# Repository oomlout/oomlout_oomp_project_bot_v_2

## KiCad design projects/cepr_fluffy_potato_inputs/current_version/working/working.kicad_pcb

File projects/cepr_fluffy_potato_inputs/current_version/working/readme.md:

# fluffy_potato
 
## summary 
* id: cepr_fluffy_potato_inputs
* user: cepr
* name: fluffy_potato
* board: inputs
* repo: https://github.com/cepr/fluffy-potato
* src_file_repo_kicad_pcb: inputs/kicad/inputs.kicad_pcb
* src_file_repo_kicad_pcb_link: https://github.com/cepr/fluffy-potato/tree/master/inputs/kicad/inputs.kicad_pcb

* src_file_repo_sch: board_generator/modules/switch-lowside-6a/switch-lowside-6a.sch
* src_file_repo_sch_link: https://github.com/cepr/fluffy-potato/tree/master/board_generator/modules/switch-lowside-6a/switch-lowside-6a.sch
* full details link: https://github.com/oomlout/oomlout_oomp_project_bot_v_2/tree/main/projects/cepr_fluffy_potato_inputs/current_version/working

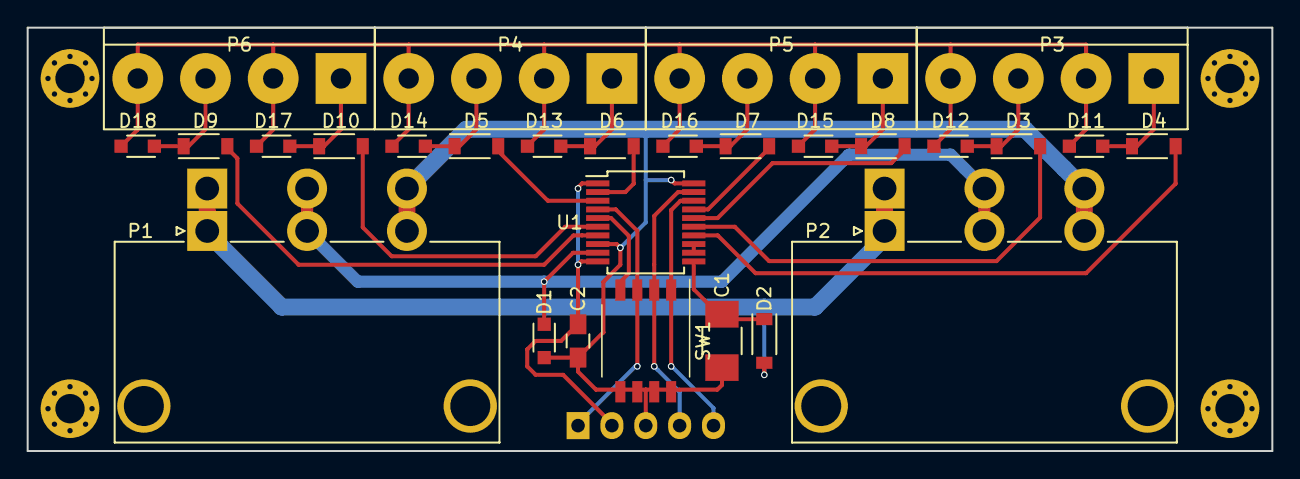
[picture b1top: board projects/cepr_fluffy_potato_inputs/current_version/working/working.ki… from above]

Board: 2 copper layers, 93.3 x 31.7 mm, 29 parts (1 on the bottom side), 26 nets.

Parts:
C1: 10uF; C_1210_HandSoldering
C2: 1uF; C_0805_HandSoldering
D1, D11, D12, D13, D14, D15, D16, D17, D18: RSB36V; SOD-323_HandSoldering
D2, D3, D4, D5, D6, D7, D8, D9, D10: 1N4148W-7-F; SOD-123
P1, P2: MOLEX-0431603103; Molex_Sabre_43160-XX03_03x7.49mm_Angled_BoardLock
P3, P4, P5, P6: TE-282836-4; bornier4
P7: CONN_01X05; Pin_Header_Angled_1x05
SW1: SW_DIP_x04; SW_DIP_x4_W7.62mm_Slide_Copal_CHS-B
U1: PIC16F1829LIN; SSOP-20_5.3x7.2mm_Pitch0.65mm

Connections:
/IN0: D4.2, U1.14
/IN1: D3.2, U1.15
/IN2: D8.2, U1.16
/IN3: D7.2, U1.17
/IN4: D6.2, U1.2
/IN5: D5.2, U1.3
/IN6: D10.2, U1.6
/IN7: D9.2, U1.7
/Sheet584DA639/+5V: C2.1, P7.2, U1.1, U1.10
/Sheet584DA639/+12V: C1.1, D2.1, U1.11
/Sheet584DA639/LBUS: D1.1, P1.2, P2.2, U1.9
/lin_common/12V_UNPROTECTED: D2.2, P1.1, P2.1
/lin_common/A0: P7.5, SW1.1, U1.18
/lin_common/A1: P7.4, SW1.2, U1.19
/lin_common/A2: P7.1, SW1.3, U1.4
/lin_common/A3: SW1.4, U1.5
GND: C1.2, C2.2, D1.2, D11.2, D12.2, D13.2, D14.2, D15.2, D16.2, D17.2, D18.2, P1.3, P2.3, P3.2, P3.4, P4.2, P4.4, P5.2, P5.4, P6.2, P6.4, P7.3, SW1.5, SW1.6, SW1.7, SW1.8, U1.8, U1.20
unnamed: D10.1, D17.1, P6.1
unnamed: D4.1, D11.1, P3.1
unnamed: D3.1, D12.1, P3.3
unnamed: D6.1, D13.1, P4.1
unnamed: D5.1, D14.1, P4.3
unnamed: D8.1, D15.1, P5.1
unnamed: D7.1, D16.1, P5.3
unnamed: D9.1, D18.1, P6.3
unnamed: U1.12, U1.13

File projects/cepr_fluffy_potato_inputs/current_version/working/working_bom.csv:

"Id";"Designator";"Footprint";"Quantity";"Designation";"Supplier and ref";
1;"C1";"C_1210_HandSoldering";1;"10uF";;;
2;"C2";"C_0805_HandSoldering";1;"1uF";;;
3;"D3,D4,D5,D6,D7,D8,D9,D10,D2";"SOD-123";9;"1N4148W-7-F";;;
4;"U1";"SSOP-20_5.3x7.2mm_Pitch0.65mm";1;"PIC16F1829LIN";;;
5;"D1,D11,D12,D13,D14,D15,D16,D17,D18";"SOD-323_HandSoldering";9;"RSB36V";;;
6;"P1,P2";"Molex_Sabre_43160-XX03_03x7.49mm_Angled_BoardLock";2;"MOLEX-0431603103";;;
7;"P3,P5,P4,P6";"bornier4";4;"TE-282836-4";;;
8;"REF**,REF**,REF**,REF**";"MountingHole_2.2mm_M2_Pad_Via";4;"MountingHole_2.2mm_M2_Pad_Via";;;
9;"SW1";"SW_DIP_x4_W7.62mm_Slide_Copal_CHS-B";1;"SW_DIP_x04";;;
10;"P7";"Pin_Header_Angled_1x05";1;"CONN_01X05";;;

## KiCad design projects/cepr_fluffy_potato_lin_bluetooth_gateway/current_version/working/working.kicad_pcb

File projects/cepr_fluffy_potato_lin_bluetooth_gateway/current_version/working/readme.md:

# fluffy_potato
 
## summary 
* id: cepr_fluffy_potato_lin_bluetooth_gateway
* user: cepr
* name: fluffy_potato
* board: lin_bluetooth_gateway
* repo: https://github.com/cepr/fluffy-potato
* src_file_repo_kicad_pcb: lin_bluetooth_gateway/kicad/lin_bluetooth_gateway.kicad_pcb
* src_file_repo_kicad_pcb_link: https://github.com/cepr/fluffy-potato/tree/master/lin_bluetooth_gateway/kicad/lin_bluetooth_gateway.kicad_pcb

* src_file_repo_sch: lin_bluetooth_gateway/kicad/lin_bluetooth_gateway.sch
* src_file_repo_sch_link: https://github.com/cepr/fluffy-potato/tree/master/lin_bluetooth_gateway/kicad/lin_bluetooth_gateway.sch
* full details link: https://github.com/oomlout/oomlout_oomp_project_bot_v_2/tree/main/projects/cepr_fluffy_potato_lin_bluetooth_gateway/current_version/working

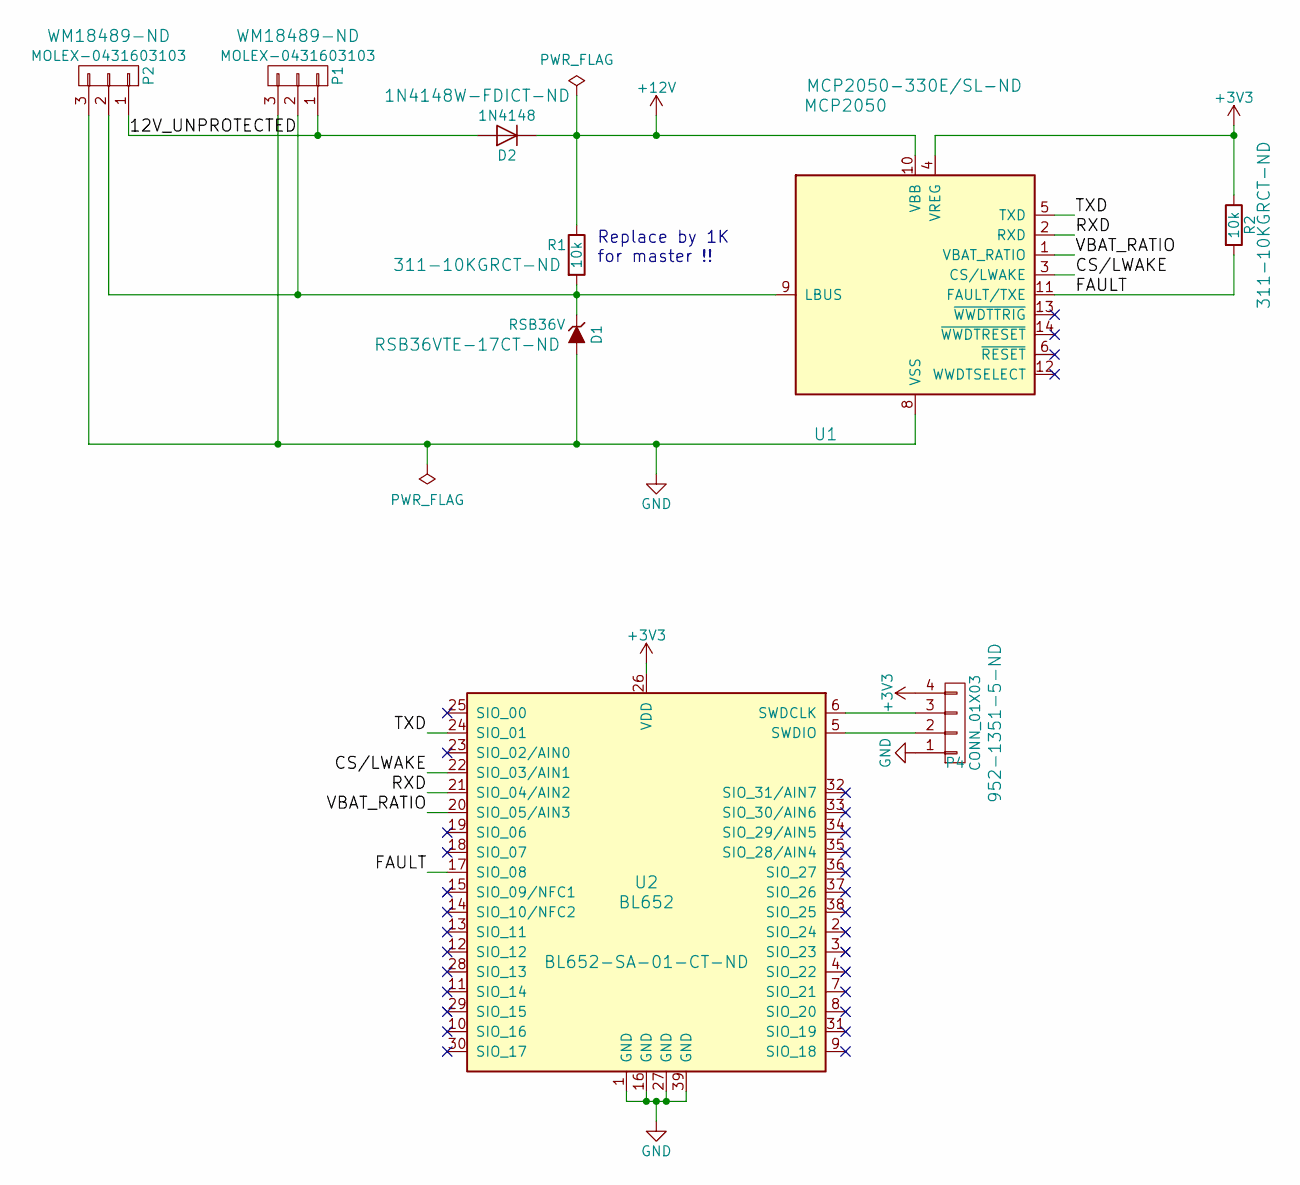
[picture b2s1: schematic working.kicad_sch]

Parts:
D1: RSB36V; SOD-323_HandSoldering; DIGIKEY RSB36VTE-17CT-ND
D2: 1N4148; SOD-123; DIGIKEY 1N4148W-FDICT-ND
P1, P2: MOLEX-0431603103; Molex_Sabre_43160-XX03_03x7.49mm_Angled_BoardLock; DIGIKEY WM18489-ND
P4: CONN_01X03; Pin_Header_Straight_1x04_Pitch2.00mm; DIGIKEY 952-1351-5-ND
R1, R2: 10k; R_0603_HandSoldering; DIGIKEY 311-10KGRCT-ND
U1: MCP2050; SOIC-14_3.9x8.7mm_Pitch1.27mm; DIGIKEY MCP2050-330E/SL-ND
U2: BL652; Laird_BL652; DIGIKEY BL652-SA-01-CT-ND

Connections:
+3V3: P4.4, R2.1, U1.4 (VREG), U2.26 (VDD)
+12V: D2.1 (K), R1.1, U1.10 (VBB)
/12V_UNPROTECTED: D2.2 (A), P1.1, P2.1
/CS/LWAKE: U1.3 (CS/LWAKE), U2.22 (SIO_03/AIN1)
/FAULT: R2.2, U1.11 (FAULT/TXE), U2.17 (SIO_08)
/RXD: U1.2 (RXD), U2.21 (SIO_04/AIN2)
/TXD: U1.5 (TXD), U2.24 (SIO_01)
/VBAT_RATIO: U1.1 (VBAT_RATIO), U2.20 (SIO_05/AIN3)
GND: D1.2 (A), P1.3, P2.3, P4.1, U1.8 (VSS), U2.1 (GND), U2.16 (GND), U2.27 (GND), U2.39 (GND)
unnamed: D1.1 (K), P1.2, P2.2, R1.2, U1.9 (LBUS)
unnamed: P4.2, U2.5 (SWDIO)
unnamed: P4.3, U2.6 (SWDCLK)

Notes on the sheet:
Replace by 1K for master !!

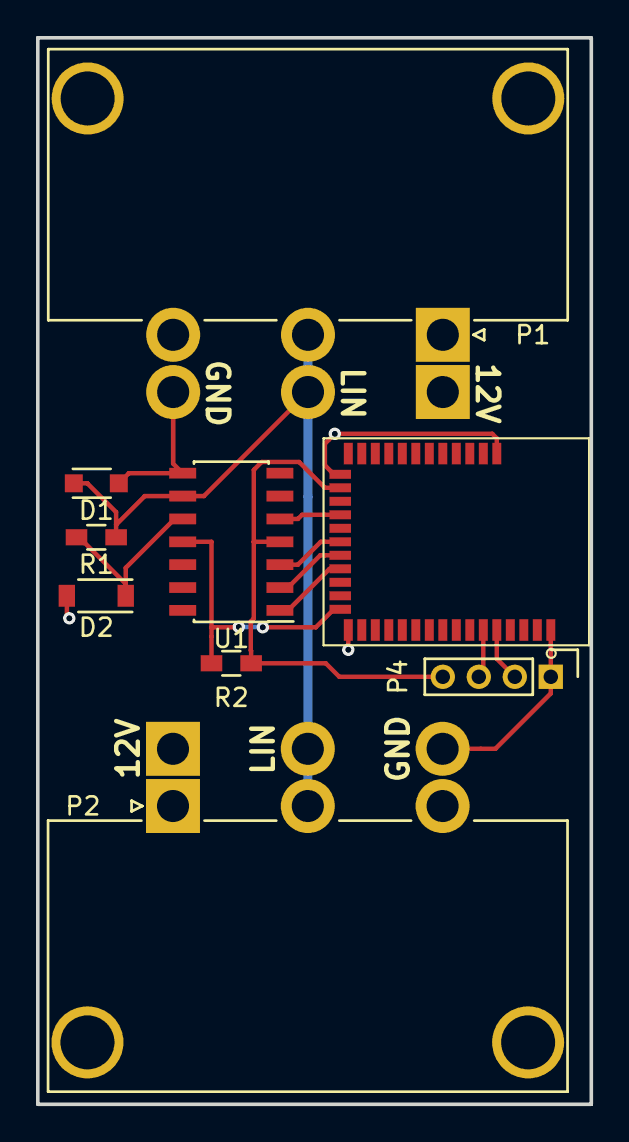
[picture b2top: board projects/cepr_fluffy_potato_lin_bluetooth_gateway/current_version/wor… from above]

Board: 2 copper layers, 30.8 x 59.2 mm, 9 parts (0 on the bottom side), 12 nets.

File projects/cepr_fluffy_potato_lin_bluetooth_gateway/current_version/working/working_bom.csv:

"Id";"Designator";"Footprint";"Quantity";"Designation";"Supplier and ref";
1;"U1";"SOIC-14_3.9x8.7mm_Pitch1.27mm";1;"MCP2050";;;
2;"R2,R1";"R_0603_HandSoldering";2;"10k";;;
3;"D1";"SOD-323_HandSoldering";1;"RSB36V";;;
4;"D2";"SOD-123";1;"1N4148";;;
5;"P4";"Pin_Header_Straight_1x04_Pitch2.00mm";1;"CONN_01X03";;;
6;"P1,P2";"Molex_Sabre_43160-XX03_03x7.49mm_Angled_BoardLock";2;"MOLEX-0431603103";;;
7;"U2";"Laird_BL652";1;"BL652";;;

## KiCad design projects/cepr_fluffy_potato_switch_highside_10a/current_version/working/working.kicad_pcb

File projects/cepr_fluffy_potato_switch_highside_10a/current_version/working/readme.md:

# fluffy_potato
 
## summary 
* id: cepr_fluffy_potato_switch_highside_10a
* user: cepr
* name: fluffy_potato
* board: switch_highside_10a
* repo: https://github.com/cepr/fluffy-potato
* src_file_repo_kicad_pcb: board_generator/modules/switch-highside-10a/switch-highside-10a.kicad_pcb
* src_file_repo_kicad_pcb_link: https://github.com/cepr/fluffy-potato/tree/master/board_generator/modules/switch-highside-10a/switch-highside-10a.kicad_pcb

* src_file_repo_sch: board_generator/modules/switch-highside-10a/switch-highside-10a.sch
* src_file_repo_sch_link: https://github.com/cepr/fluffy-potato/tree/master/board_generator/modules/switch-highside-10a/switch-highside-10a.sch
* full details link: https://github.com/oomlout/oomlout_oomp_project_bot_v_2/tree/main/projects/cepr_fluffy_potato_switch_highside_10a/current_version/working

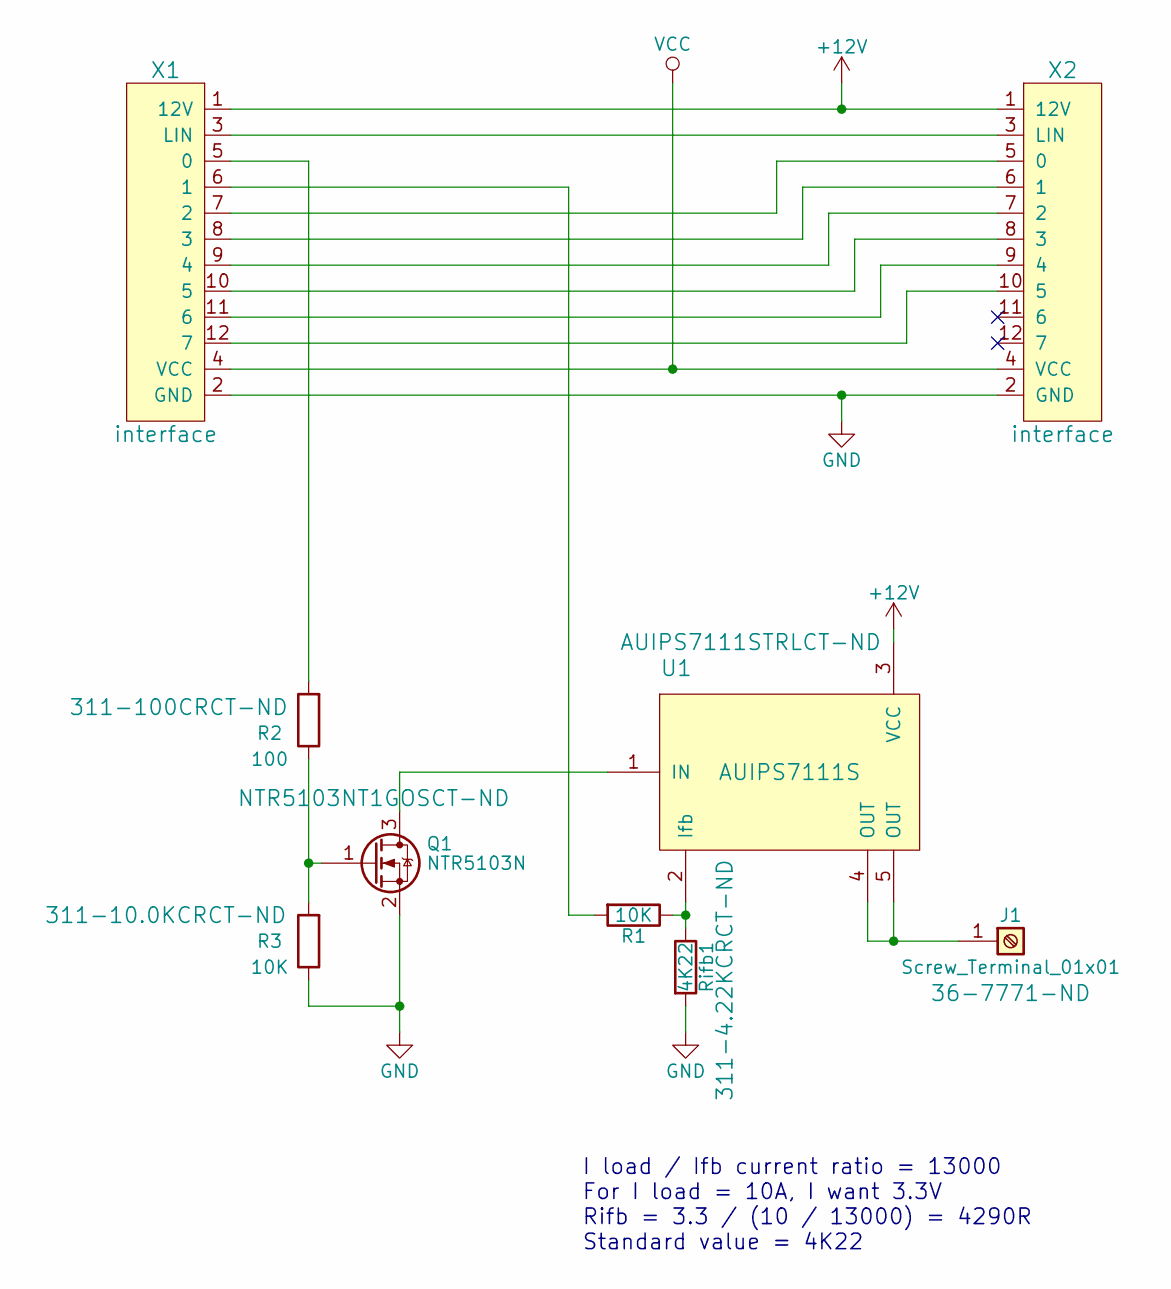
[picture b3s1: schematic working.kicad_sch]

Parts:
J1: Screw_Terminal_01x01; TERM_SCREW_M3; DIGIKEY 36-7771-ND
Q1: NTR5103N; SOT-23; DIGIKEY NTR5103NT1GOSCT-ND
R1, R3: 10K; R_0805_HandSoldering; DIGIKEY 311-10.0KCRCT-ND
R2: 100; R_0805_HandSoldering; DIGIKEY 311-100CRCT-ND
Rifb1: 4K22; R_0805_HandSoldering; DIGIKEY 311-4.22KCRCT-ND
U1: AUIPS7111S; TO-263-5_TabPin3; DIGIKEY AUIPS7111STRLCT-ND
X1, X2: interface

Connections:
+12V: U1.3 (VCC), X1.1 (12V), X2.1 (12V)
GND: Q1.2 (S), R3.1, Rifb1.2, X1.2 (GND), X2.2 (GND)
unnamed: J1.1, U1.4 (OUT), U1.5 (OUT)
unnamed: Q1.1 (G), R2.1, R3.2
unnamed: Q1.3 (D), U1.1 (IN)
unnamed: R1.1, Rifb1.1, U1.2 (Ifb)
unnamed: R1.2, X1.6 (1)
unnamed: R2.2, X1.5 (0)
unnamed: X1.3 (LIN), X2.3 (LIN)
unnamed: X1.7 (2), X2.5 (0)
unnamed: X1.8 (3), X2.6 (1)
unnamed: X1.9 (4), X2.7 (2)
unnamed: X1.10 (5), X2.8 (3)
unnamed: X1.11 (6), X2.9 (4)
unnamed: X1.12 (7), X2.10 (5)
VCC: X1.4 (VCC), X2.4 (VCC)

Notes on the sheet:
I load / Ifb current ratio = 13000 For I load = 10A, I want 3.3V Rifb = 3.3 / (10 / 13000) = 4290R Standard value = 4K22

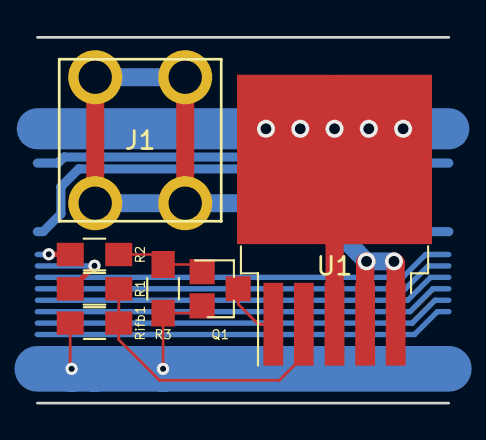
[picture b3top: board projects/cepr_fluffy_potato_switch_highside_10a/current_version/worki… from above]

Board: 2 copper layers, 22.9 x 20.3 mm, 9 parts (0 on the bottom side), 16 nets.

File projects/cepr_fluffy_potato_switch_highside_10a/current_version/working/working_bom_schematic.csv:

"Source:","C:\gh\oomlout_oomp_project_bot_v_2\projects\cepr_fluffy_potato_switch_highside_10a\current_version\working\working.kicad_sch"
"Date:","28/09/2023 17:09:21"
"Tool:","Eeschema 7.0.6"
"Generator:","C:/Program Files/KiCad/7.0/bin/scripting/plugins/bom_csv_grouped_by_value_with_fp.py"
"Component Count:","9"
"Ref","Qnty","Value","Cmp name","Footprint","Description","Vendor","DNP"
"J1","1","Screw_Terminal_01x01","Screw_Terminal_01x01","connectors:TERM_SCREW_M3","","",""
"Q1","1","NTR5103N","2N7002","TO_SOT_Packages_SMD:SOT-23","","",""
"R1, R3","2","10K","R","Resistors_SMD:R_0805_HandSoldering","","",""
"R2","1","100","R","Resistors_SMD:R_0805_HandSoldering","","",""
"Rifb1","1","4K22","R","Resistors_SMD:R_0805_HandSoldering","","",""
"U1","1","AUIPS7111S","AUIPS7111S","TO_SOT_Packages_SMD:TO-263-5_TabPin3","CURRENT SENSE HIGH SIDE SWITCH","",""
"X1, X2","2","interface","interface","interface:interface","","",""

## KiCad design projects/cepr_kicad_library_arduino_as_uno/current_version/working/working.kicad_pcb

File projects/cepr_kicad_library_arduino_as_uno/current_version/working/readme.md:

# kicad_library
 
## summary 
* id: cepr_kicad_library_arduino_as_uno
* user: cepr
* name: kicad_library
* board: arduino_as_uno
* repo: https://github.com/cepr/kicad-library
* src_file_repo_kicad_pcb: template/Arduino_As_Uno_R3/Arduino_As_Uno.kicad_pcb
* src_file_repo_kicad_pcb_link: https://github.com/cepr/kicad-library/tree/master/template/Arduino_As_Uno_R3/Arduino_As_Uno.kicad_pcb

* src_file_repo_sch: template/Arduino_As_Uno_R3/Arduino_As_Uno.sch
* src_file_repo_sch_link: https://github.com/cepr/kicad-library/tree/master/template/Arduino_As_Uno_R3/Arduino_As_Uno.sch
* full details link: https://github.com/oomlout/oomlout_oomp_project_bot_v_2/tree/main/projects/cepr_kicad_library_arduino_as_uno/current_version/working

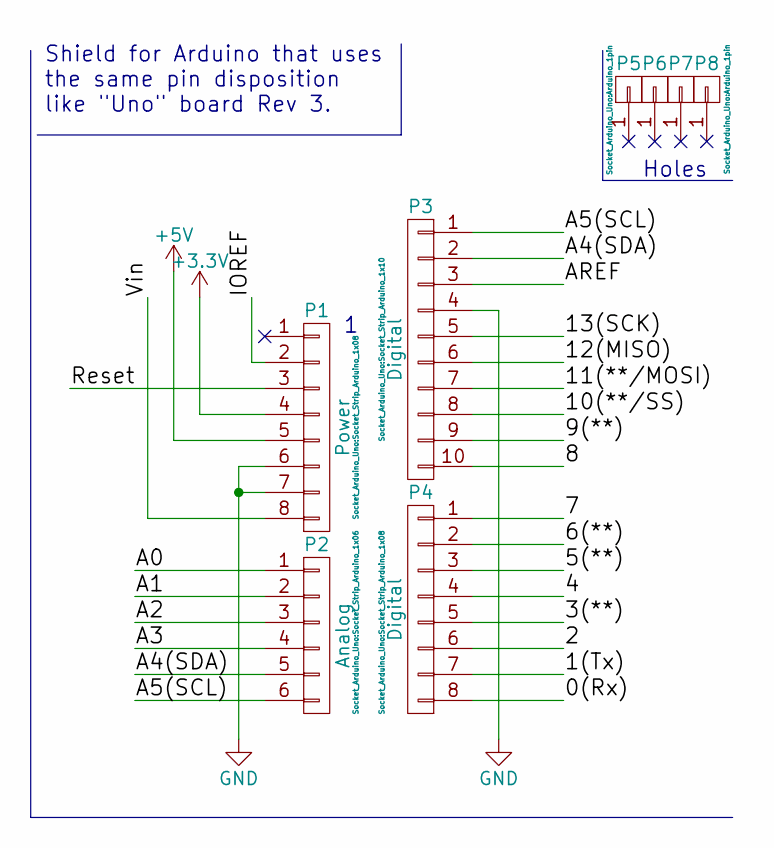
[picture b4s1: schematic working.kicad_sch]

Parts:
P1: Power; Socket_Strip_Arduino_1x08
P2: Analog; Socket_Strip_Arduino_1x06
P3: Digital; Socket_Strip_Arduino_1x10
P4: Digital; Socket_Strip_Arduino_1x08
P5, P6, P7, P8: CONN_01X01; Arduino_1pin

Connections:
+3V3: P1.4
+5V: P1.5
/0(Rx): P4.8
/1(Tx): P4.7
/2: P4.6
/3(**): P4.5
/4: P4.4
/5(**): P4.3
/6(**): P4.2
/7: P4.1
/8: P3.10
/9(**): P3.9
/10(**/SS): P3.8
/11(**/MOSI): P3.7
/12(MISO): P3.6
/13(SCK): P3.5
/A0: P2.1
/A1: P2.2
/A2: P2.3
/A3: P2.4
/A4(SDA): P2.5, P3.2
/A5(SCL): P2.6, P3.1
/AREF: P3.3
/IOREF: P1.2
/Reset: P1.3
/Vin: P1.8
GND: P1.6, P1.7, P3.4

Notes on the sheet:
Shield for Arduino that uses the same pin disposition like "Uno" board Rev 3.
Holes

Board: 2 copper layers, 8 parts (0 on the bottom side), 3 nets, no tracks yet.

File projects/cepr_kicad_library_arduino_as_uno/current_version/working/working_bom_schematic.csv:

"Source:","C:\gh\oomlout_oomp_project_bot_v_2\projects\cepr_kicad_library_arduino_as_uno\current_version\working\working.kicad_sch"
"Date:","28/09/2023 17:33:03"
"Tool:","Eeschema 7.0.6"
"Generator:","C:/Program Files/KiCad/7.0/bin/scripting/plugins/bom_csv_grouped_by_value_with_fp.py"
"Component Count:","8"
"Ref","Qnty","Value","Cmp name","Footprint","Description","Vendor","DNP"
"P1","1","Power","CONN_01X08","Socket_Arduino_Uno:Socket_Strip_Arduino_1x08","","",""
"P2","1","Analog","CONN_01X06","Socket_Arduino_Uno:Socket_Strip_Arduino_1x06","","",""
"P3","1","Digital","CONN_01X10","Socket_Arduino_Uno:Socket_Strip_Arduino_1x10","","",""
"P4","1","Digital","CONN_01X08","Socket_Arduino_Uno:Socket_Strip_Arduino_1x08","","",""
"P5, P6, P7, P8","4","CONN_01X01","CONN_01X01","Socket_Arduino_Uno:Arduino_1pin","","",""

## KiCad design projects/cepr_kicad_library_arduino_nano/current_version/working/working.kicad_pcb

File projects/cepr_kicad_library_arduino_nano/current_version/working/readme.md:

# kicad_library
 
## summary 
* id: cepr_kicad_library_arduino_nano
* user: cepr
* name: kicad_library
* board: arduino_nano
* repo: https://github.com/cepr/kicad-library
* src_file_repo_kicad_pcb: template/Arduino_Nano/Arduino_Nano.kicad_pcb
* src_file_repo_kicad_pcb_link: https://github.com/cepr/kicad-library/tree/master/template/Arduino_Nano/Arduino_Nano.kicad_pcb

* src_file_repo_sch: template/Arduino_Nano/Arduino_Nano.sch
* src_file_repo_sch_link: https://github.com/cepr/kicad-library/tree/master/template/Arduino_Nano/Arduino_Nano.sch
* full details link: https://github.com/oomlout/oomlout_oomp_project_bot_v_2/tree/main/projects/cepr_kicad_library_arduino_nano/current_version/working

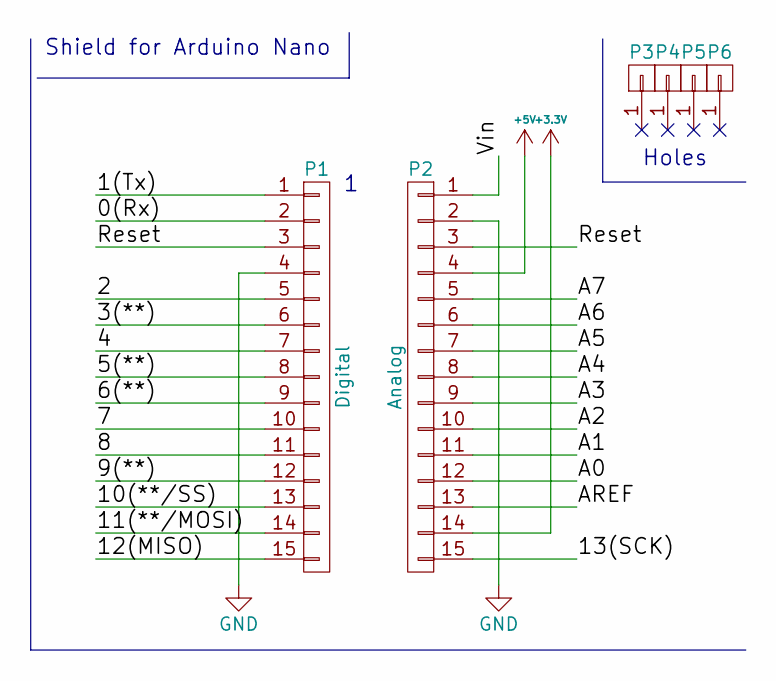
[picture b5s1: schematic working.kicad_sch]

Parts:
P1: Digital; Socket_Strip_Arduino_1x15
P2: Analog; Socket_Strip_Arduino_1x15
P3, P4, P5, P6: CONN_01X01; 1pin_Nano

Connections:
+3V3: P2.14
+5V: P2.4
/0(Rx): P1.2
/1(Tx): P1.1
/2: P1.5
/3(**): P1.6
/4: P1.7
/5(**): P1.8
/6(**): P1.9
/7: P1.10
/8: P1.11
/9(**): P1.12
/10(**/SS): P1.13
/11(**/MOSI): P1.14
/12(MISO): P1.15
/13(SCK): P2.15
/A0: P2.12
/A1: P2.11
/A2: P2.10
/A3: P2.9
/A4: P2.8
/A5: P2.7
/A6: P2.6
/A7: P2.5
/AREF: P2.13
/Reset: P1.3, P2.3
/Vin: P2.1
GND: P1.4, P2.2

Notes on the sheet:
Shield for Arduino Nano
Holes

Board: 2 copper layers, 6 parts (0 on the bottom side), 2 nets, no tracks yet.

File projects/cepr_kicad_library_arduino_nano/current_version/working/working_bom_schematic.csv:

"Source:","C:\gh\oomlout_oomp_project_bot_v_2\projects\cepr_kicad_library_arduino_nano\current_version\working\working.kicad_sch"
"Date:","28/09/2023 18:12:34"
"Tool:","Eeschema 7.0.6"
"Generator:","C:/Program Files/KiCad/7.0/bin/scripting/plugins/bom_csv_grouped_by_value_with_fp.py"
"Component Count:","6"
"Ref","Qnty","Value","Cmp name","Footprint","Description","Vendor","DNP"
"P1","1","Digital","CONN_01X15","Socket_Arduino_Nano:Socket_Strip_Arduino_1x15","","",""
"P2","1","Analog","CONN_01X15","Socket_Arduino_Nano:Socket_Strip_Arduino_1x15","","",""
"P3, P4, P5, P6","4","CONN_01X01","CONN_01X01","Socket_Arduino_Nano:1pin_Nano","","",""
